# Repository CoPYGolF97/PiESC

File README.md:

# PiESC

**An independent open-source ESC project for RP2350.**

### PiESC S1 PCB 20×50

| Front                                                              | Back                                                              |
| ------------------------------------------------------------------ | ----------------------------------------------------------------- |
|  |  |

---
### PiESC 4in1 45X50

| Front                                                              | Back                                                              |
| ------------------------------------------------------------------ | ----------------------------------------------------------------- |
|  |  |

---
## English

**PiESC** is an open-source Electronic Speed Controller (ESC): the board that drives the brushless motors of a drone or other multirotor aircraft. It is built around the **RP2350** microcontroller (the chip family of the Raspberry Pi Pico 2). The name comes from "Pi" (RP2350 / Pi Pico family) + "ESC".

PiESC is an open-source project exploring the design and development of ESC firmware and hardware using the RP2350 microcontroller.

The goal is to create another open-source option for ESC development, learning, experimentation, and future community collaboration.

### Project Status

🚧 **Early Development**

PiESC is currently an experimental project.

The hardware and firmware are being developed and tested step by step. Features, circuit designs, firmware architecture, and documentation may change during development.

Nothing here has been run on a motor or flown yet.

⚠️ This design handles high current from lithium batteries. Mistakes can cause fire or damage. Build and test at your own risk: start with a current-limited power supply, and never leave it unattended.

| Item | State |
| --- | --- |
| PiESC S1 PCB 20×50 (first single-ESC board) | Designed, files in this repository |
| PiESC 1CH Test (1-motor, 2-layer test board) | Design finished, DRC clean. **Not yet ordered or tested** |
| PiESC 4-in-1 V4, 45×50 mm (2× RP2350B, 6-layer HDI) | Layout finished, DRC clean. **Not yet ordered or tested** |
| Firmware on a Raspberry Pi Pico 2 dev board | LED blink, USB serial, 3 complementary PWM pairs at 20 kHz with dead-time, open-loop 6-step commutation (checked with a multimeter, **not** with a motor) |
| Not done yet | DShot input, back-EMF / sensorless control, current sensing, protection (over-current, under-voltage, watchdog), telemetry |

Design files for the 1CH test board and the 4-in-1 board will be added to this repository.

### Hardware

The initial development platform uses the **RP2350** microcontroller.

Development hardware is purchased independently by the project creator.

PiESC is an independent project and is **not affiliated with, sponsored by, or endorsed by Raspberry Pi Ltd.**

### Firmware

The firmware is being developed with a focus on:

* 3-phase BLDC motor control
* PWM generation
* Motor commutation
* MOSFET gate-driver control
* Current sensing
* Motor protection
* Future sensorless control
* Future ESC telemetry and configuration

### Open Source

PiESC is intended to be an open-source project.

We welcome developers, electronics enthusiasts, researchers, makers, and anyone interested in motor control to explore the project and contribute ideas, testing, documentation, hardware designs, or code.

### How you can help
PiESC is incomplete, so help is very welcome. Good places to start:
- Review the schematics and PCB layouts (1CH Test board, 4-in-1 V4) and report mistakes
- Write a DShot decoder using the RP2350 PIO
- Back-EMF zero-crossing / sensorless control
- Protection: over-current, under-voltage, watchdog
- Telemetry over UART
- Documentation, pinouts, bring-up guides

See [CONTRIBUTING.md](CONTRIBUTING.md) and the Issues tab.

### License

This project is licensed under the **GNU General Public License v3.0**. See the [`LICENSE`](LICENSE) file.

### Development

The project is being developed using:

* RP2350 / Raspberry Pi Pico 2
* PlatformIO
* Pico SDK
* C/C++
* KiCad

### A Personal Project

PiESC was started by an ordinary electronics enthusiast who wanted to learn, experiment, and build something that others could continue developing.

The project creator is not a professional software engineer or electrical engineer. Much of the development process is based on learning through experimentation, documentation, community knowledge, and AI-assisted development.

**AI assistants are used in this project: ChatGPT in the early stage, and Claude (Anthropic) for design review, guidance, programming, debugging, and documentation. The PCBs are drawn by the project creator, and hardware is built and tested step by step as it becomes available. The creator reviews what the AI suggests, but it may still contain mistakes.**

The goal is not to claim that everything is perfect.

The goal is to build something useful, learn along the way, and make the work available for others to improve.

---

## ภาษาไทย

**PiESC** คือ Electronic Speed Controller (ESC) แบบโอเพนซอร์ส เป็นบอร์ดที่ควบคุมมอเตอร์ไร้แปรงถ่านของโดรนหรืออากาศยานมัลติโรเตอร์ สร้างบนไมโครคอนโทรลเลอร์ **RP2350** (ชิปตระกูลเดียวกับ Raspberry Pi Pico 2) ชื่อมาจาก "Pi" (ตระกูล RP2350 / Pi Pico) รวมกับ "ESC"

PiESC คือโปรเจกต์ Open Source ที่กำลังศึกษาและพัฒนา Firmware และ Hardware สำหรับ ESC โดยใช้ไมโครคอนโทรลเลอร์ RP2350

เป้าหมายของเราคือการสร้างทางเลือกอีกทางหนึ่งสำหรับการพัฒนา ESC แบบ Open Source เพื่อการเรียนรู้ การทดลอง และเปิดโอกาสให้ชุมชนเข้ามาช่วยพัฒนาต่อในอนาคต

### สถานะโปรเจกต์

🚧 **อยู่ในช่วงเริ่มต้นของการพัฒนา**

ขณะนี้ PiESC ยังเป็นโปรเจกต์สำหรับการทดลองและพัฒนา

Hardware และ Firmware กำลังถูกพัฒนาและทดสอบทีละขั้นตอน ดังนั้นคุณสมบัติ วงจร โครงสร้าง Firmware และเอกสารต่าง ๆ อาจมีการเปลี่ยนแปลงระหว่างการพัฒนา

ยังไม่เคยต่อมอเตอร์หรือบินจริง

⚠️ การออกแบบนี้ใช้กระแสสูงจากแบตเตอรี่ลิเธียม ความผิดพลาดอาจทำให้เกิดไฟไหม้หรือความเสียหาย สร้างและทดสอบด้วยความเสี่ยงของตัวเอง เริ่มต้นด้วยแหล่งจ่ายไฟจำกัดกระแส และไม่ปล่อยทิ้งไว้โดยไม่มีคนดู

| รายการ | สถานะ |
| --- | --- |
| PiESC S1 PCB 20×50 (บอร์ด ESC ตัวแรก) | ออกแบบแล้ว ไฟล์อยู่ใน repository นี้ |
| PiESC 1CH Test (บอร์ดทดสอบ 1 มอเตอร์ 2 ชั้น) | ออกแบบเสร็จ DRC ผ่าน **ยังไม่ได้สั่งผลิตและยังไม่ได้ทดสอบ** |
| PiESC 4-in-1 V4 ขนาด 45×50 mm (RP2350B 2 ตัว, HDI 6 ชั้น) | วางลายเสร็จ DRC ผ่าน **ยังไม่ได้สั่งผลิตและยังไม่ได้ทดสอบ** |
| Firmware บนบอร์ด Raspberry Pi Pico 2 | LED กะพริบ, USB serial, PWM 3 คู่ 20 kHz พร้อม dead-time, คอมมิวเทต 6 สเต็ปแบบ open-loop (ตรวจด้วยมัลติมิเตอร์ **ยังไม่ได้ต่อมอเตอร์**) |
| ยังไม่ได้ทำ | รับสัญญาณ DShot, BEMF / sensorless, การวัดกระแส, ระบบป้องกัน (กระแสเกิน แรงดันต่ำ watchdog), Telemetry |

ไฟล์ออกแบบของบอร์ด 1CH Test และ 4-in-1 จะทยอยเพิ่มใน repository นี้

### Hardware

แพลตฟอร์มเริ่มต้นของโปรเจกต์ใช้ไมโครคอนโทรลเลอร์ **RP2350**

Hardware ที่ใช้ในการพัฒนาถูกจัดซื้อโดยผู้ริเริ่มโปรเจกต์เอง

PiESC เป็นโปรเจกต์อิสระ และ **ไม่มีความเกี่ยวข้อง ได้รับการสนับสนุน หรือได้รับการรับรองจาก Raspberry Pi Ltd.**

### Firmware

Firmware กำลังได้รับการพัฒนาโดยมุ่งเน้นไปที่:

* การควบคุมมอเตอร์ BLDC แบบ 3 เฟส
* การสร้าง PWM
* การ Commutation ของมอเตอร์
* การควบคุม MOSFET Gate Driver
* การวัดกระแส
* ระบบป้องกันมอเตอร์และ ESC
* การควบคุมแบบ Sensorless ในอนาคต
* Telemetry และการตั้งค่า ESC ในอนาคต

### Open Source

PiESC ตั้งใจให้เป็นโปรเจกต์ Open Source

เรายินดีต้อนรับนักพัฒนา ผู้สนใจอิเล็กทรอนิกส์ นักวิจัย Maker และทุกคนที่สนใจด้านการควบคุมมอเตอร์ ให้เข้ามาศึกษา ทดลอง เสนอแนวคิด ทดสอบ ปรับปรุงเอกสาร Hardware หรือ Firmware และช่วยพัฒนาโปรเจกต์ต่อ

### ช่วยเราได้อย่างไร
PiESC ยังไม่สมบูรณ์ ยินดีรับความช่วยเหลือมาก ตัวอย่างงานที่เริ่มได้:
- ตรวจ Schematic และ PCB (บอร์ดทดสอบ 1CH, 4-in-1 V4) และแจ้งข้อผิดพลาด
- เขียนตัวถอดรหัส DShot ด้วย PIO ของ RP2350
- BEMF zero-crossing / การควบคุมแบบ sensorless
- ระบบป้องกัน: กระแสเกิน แรงดันต่ำ watchdog
- Telemetry ผ่าน UART
- เอกสาร พินเอาต์ และคู่มือทดสอบบอร์ดครั้งแรก

ดู [CONTRIBUTING.md](CONTRIBUTING.md) และแท็บ Issues
### ใบอนุญาต (License)

โปรเจกต์นี้ใช้ใบอนุญาต **GNU General Public License v3.0** ดูรายละเอียดในไฟล์ [`LICENSE`](LICENSE)

### เครื่องมือที่ใช้ในการพัฒนา

โปรเจกต์นี้ใช้:

* RP2350 / Raspberry Pi Pico 2
* PlatformIO
* Pico SDK
* C/C++
* KiCad

### จุดเริ่มต้นของโปรเจกต์

PiESC เริ่มต้นจากคนธรรมดาที่สนใจอิเล็กทรอนิกส์ และต้องการเรียนรู้ ทดลอง และสร้างสิ่งที่คนอื่นสามารถเข้ามาช่วยพัฒนาต่อได้

ผู้ริเริ่มโปรเจกต์ไม่ได้เป็นวิศวกรซอฟต์แวร์หรือวิศวกรไฟฟ้ามืออาชีพ การพัฒนาส่วนหนึ่งเกิดจากการเรียนรู้ผ่านการทดลอง การศึกษาข้อมูล ความรู้จากชุมชน และการใช้ AI ช่วยในการพัฒนา

**โปรเจกต์นี้ใช้ AI เป็นผู้ช่วย: ช่วงแรกใช้ ChatGPT และต่อมาใช้ Claude (Anthropic) ช่วยตรวจแบบ ให้คำแนะนำ เขียนโปรแกรม แก้ไขข้อผิดพลาด และจัดทำเอกสาร ผู้ริเริ่มโปรเจกต์เป็นผู้วาด PCB และสร้าง/ทดสอบฮาร์ดแวร์ทีละขั้นเมื่อมีของพร้อม ตรวจทานสิ่งที่ AI เสนอ แต่ยังอาจมีข้อผิดพลาดได้**

เราไม่ได้อ้างว่าโปรเจกต์นี้สมบูรณ์แบบ

เป้าหมายคือการสร้างสิ่งที่มีประโยชน์ เรียนรู้ไปพร้อมกับการพัฒนา และเปิดผลงานให้ผู้อื่นสามารถเข้ามาช่วยปรับปรุงต่อได้

---

**PiESC — Build it. Test it. Improve it.**

**PiESC — สร้าง ทดลอง และพัฒนาไปด้วยกัน**

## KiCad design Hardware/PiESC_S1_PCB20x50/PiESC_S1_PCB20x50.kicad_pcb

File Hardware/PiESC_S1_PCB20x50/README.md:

# PiESC S1 PCB 20×50

Initial hardware design for the PiESC project.

## Specifications

* Board size: 20 × 50 mm
* 4-layer PCB
* Target current: 30A / 45A
* 3-phase brushless motor ESC
* RP2350-based control platform
* Battery voltage target: approximately 12–16 V

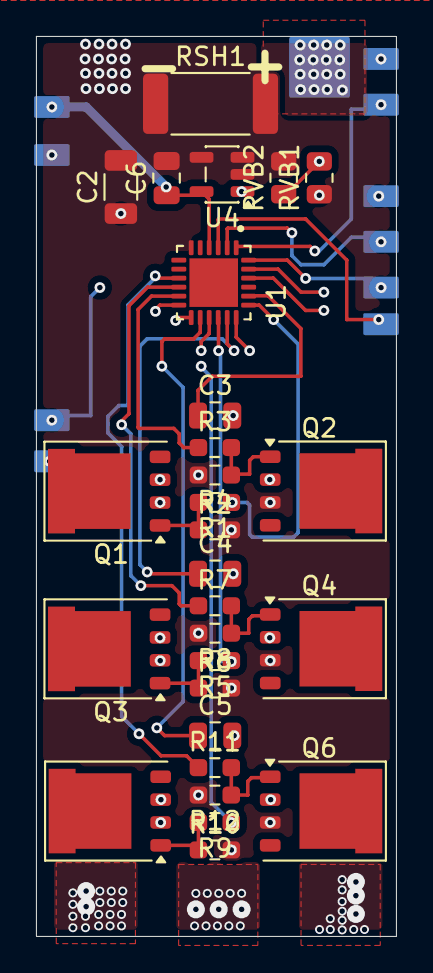
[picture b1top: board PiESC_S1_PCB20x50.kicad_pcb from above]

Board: 4 copper layers, 20.0 x 50.0 mm, 28 parts (0 on the bottom side), 22 nets.

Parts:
C2: 10uF 50V MLCC; C_1206_3216Metric
C3, C4, C5, C6: 100nF 50V MLCC; C_0805_2012Metric
Q1, Q2, Q3, Q4, Q5, Q6: AON34356; PQFN-8-EP_6x5mm_P1.27mm_Generic
R1, R3, R5, R7, R9, R11: 10R; R_0603_1608Metric_Pad0.98x0.95mm_HandSolder
R2, R4, R6, R8, R10, R12: 100k; R_0603_1608Metric_Pad0.98x0.95mm_HandSolder
RSH1: 2mΩ; R_2512_6332Metric_Pad1.40x3.35mm_HandSolder
RVB1: 100k; R_0805_2012Metric
RVB2: 20k; R_0805_2012Metric
U1: FD6288Q; QFN50P400X400X90-25N
U4: INA180A2; SOT-23-5

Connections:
+5V: C6.1, U1.4 (VCC), U4.5 (V+)
/PHASE_U: C3.2, Q1.3 (S), Q2.2 (D), U1.18 (VS1)
/PHASE_V: C4.2, Q3.3 (S), Q4.2 (D), U1.15 (VS2)
/PHASE_W: C5.2, Q5.3 (S), Q6.2 (D), U1.12 (VS3)
/VBAT+: Q1.2 (D), Q3.2 (D), Q5.2 (D)
GND: C2.1, C2.2, C6.2, Q2.3 (S), Q4.3 (S), Q6.3 (S), R2.2, R4.2, R6.2, R8.2, R10.2, R12.2, RSH1.1, RSH1.2, RVB1.1, RVB2.2, U1.6 (COM), U1.25 (EXP), U4.2 (GND), U4.3 (+), U4.4 (-)
unnamed: RVB1.2, RVB2.1
unnamed: Q1.1 (G), R1.2, R2.1
unnamed: Q2.1 (G), R3.2, R4.1
unnamed: Q3.1 (G), R5.2, R6.1
unnamed: Q4.1 (G), R7.2, R8.1
unnamed: Q5.1 (G), R9.2, R10.1
unnamed: Q6.1 (G), R11.2, R12.1
unnamed: R1.1, U1.19 (HO1)
unnamed: R5.1, U1.16 (HO2)
unnamed: R9.1, U1.13 (HO3)
unnamed: R3.1, U1.11 (LO1)
unnamed: R7.1, U1.10 (LO2)
unnamed: R11.1, U1.9 (LO3)
unnamed: C3.1, U1.20 (VB1)
unnamed: C4.1, U1.17 (VB2)
unnamed: C5.1, U1.14 (VB3)
